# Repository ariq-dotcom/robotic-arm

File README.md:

Repository ini berisi file-file pengembangan robot arm 5 DOF berbasis Arduino Mega, meliputi desain elektrikal (PCB), program kendali

Pada folder ARM KENDALI, setiap angka pada nama file .ino menunjukkan urutan perkembangan dan pembaruan program sejak tahap awal pengembangan ketika isi program masih berupa struktur dasar dan belum sepenuhnya siap digunakan. File dengan angka terbesar merupakan program versi terbaru.

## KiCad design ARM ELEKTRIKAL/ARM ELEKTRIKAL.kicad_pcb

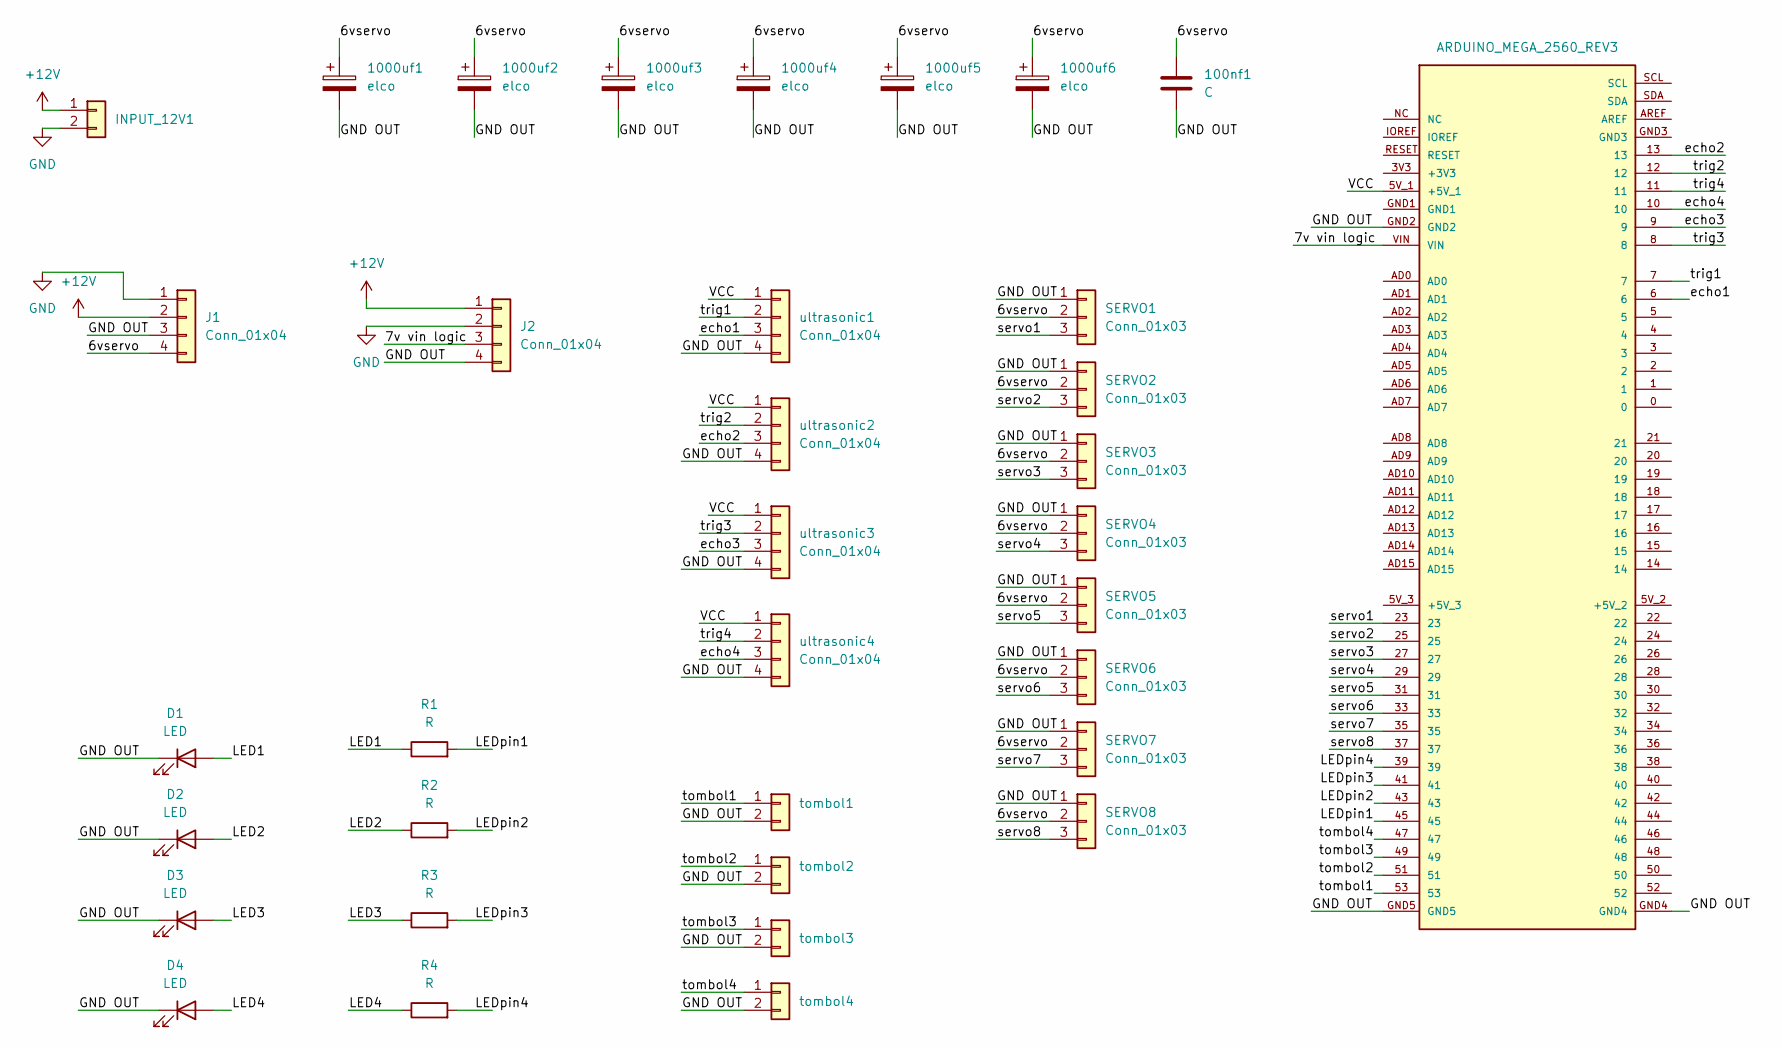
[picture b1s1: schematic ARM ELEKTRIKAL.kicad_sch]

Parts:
100nf1: C; C_Rect_L9.0mm_W2.7mm_P7.50mm_MKT
1000uf1, 1000uf2, 1000uf3, 1000uf4, 1000uf5, 1000uf6: elco; CP_Radial_D10.0mm_P5.00mm
A1: ARDUINO_MEGA_2560_REV3; ARDUINO_ARDUINO_MEGA_2560_REV3; PARTREV 3
D1, D2, D3, D4: LED; PinHeader_1x02_P2.54mm_Vertical
INPUT_12V1: Conn_01x02; TerminalBlock_MetzConnect_Type171_RT13702HBWC_1x02_P7.50mm_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
J1, J2: Conn_01x04; TerminalBlock_MetzConnect_Type171_RT13704HBWC_1x04_P7.50mm_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
R1, R2, R3, R4: R; R_Axial_DIN0204_L3.6mm_D1.6mm_P7.62mm_Horizontal
SERVO1, SERVO2, SERVO3, SERVO4, SERVO5, SERVO6, SERVO7, SERVO8: Conn_01x03; PinHeader_1x03_P2.54mm_Vertical
tombol1, tombol2, tombol3, tombol4: Conn_01x02; PinHeader_1x02_P2.54mm_Vertical
ultrasonic1, ultrasonic2, ultrasonic3, ultrasonic4: Conn_01x04; PinHeader_1x04_P2.54mm_Vertical

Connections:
+12V: INPUT_12V1.1, J1.2, J2.1
/6vservo: 100nf1.1, 1000uf1.1, 1000uf2.1, 1000uf3.1, 1000uf4.1, 1000uf5.1, 1000uf6.1, J1.4, SERVO1.2, SERVO2.2, SERVO3.2, SERVO4.2, SERVO5.2, SERVO6.2, SERVO7.2, SERVO8.2
/7v vin logic: A1.VIN, J2.3
/GND OUT: 100nf1.2, 1000uf1.2, 1000uf2.2, 1000uf3.2, 1000uf4.2, 1000uf5.2, 1000uf6.2, A1.GND2, A1.GND4, A1.GND5, D1.1 (K), D2.1 (K), D3.1 (K), D4.1 (K), J1.3, J2.4, SERVO1.1, SERVO2.1, SERVO3.1, SERVO4.1, SERVO5.1, SERVO6.1, SERVO7.1, SERVO8.1, tombol1.2, tombol2.2, tombol3.2, tombol4.2, ultrasonic1.4, ultrasonic2.4, ultrasonic3.4, ultrasonic4.4
/LED1: D1.2 (A), R1.1
/LED2: D2.2 (A), R2.1
/LED3: D3.2 (A), R3.1
/LED4: D4.2 (A), R4.1
/LEDpin1: A1.45, R1.2
/LEDpin2: A1.43, R2.2
/LEDpin3: A1.41, R3.2
/LEDpin4: A1.39, R4.2
/VCC: A1.5V_1 (+5V_1), ultrasonic1.1, ultrasonic2.1, ultrasonic3.1, ultrasonic4.1
/echo1: A1.6, ultrasonic1.3
/echo2: A1.13, ultrasonic2.3
/echo3: A1.9, ultrasonic3.3
/echo4: A1.10, ultrasonic4.3
/servo1: A1.23, SERVO1.3
/servo2: A1.25, SERVO2.3
/servo3: A1.27, SERVO3.3
/servo4: A1.29, SERVO4.3
/servo5: A1.31, SERVO5.3
/servo6: A1.33, SERVO6.3
/servo7: A1.35, SERVO7.3
/servo8: A1.37, SERVO8.3
/tombol1: A1.53, tombol1.1
/tombol2: A1.51, tombol2.1
/tombol3: A1.49, tombol3.1
/tombol4: A1.47, tombol4.1
/trig1: A1.7, ultrasonic1.2
/trig2: A1.12, ultrasonic2.2
/trig3: A1.8, ultrasonic3.2
/trig4: A1.11, ultrasonic4.2
GND: INPUT_12V1.2, J1.1, J2.2

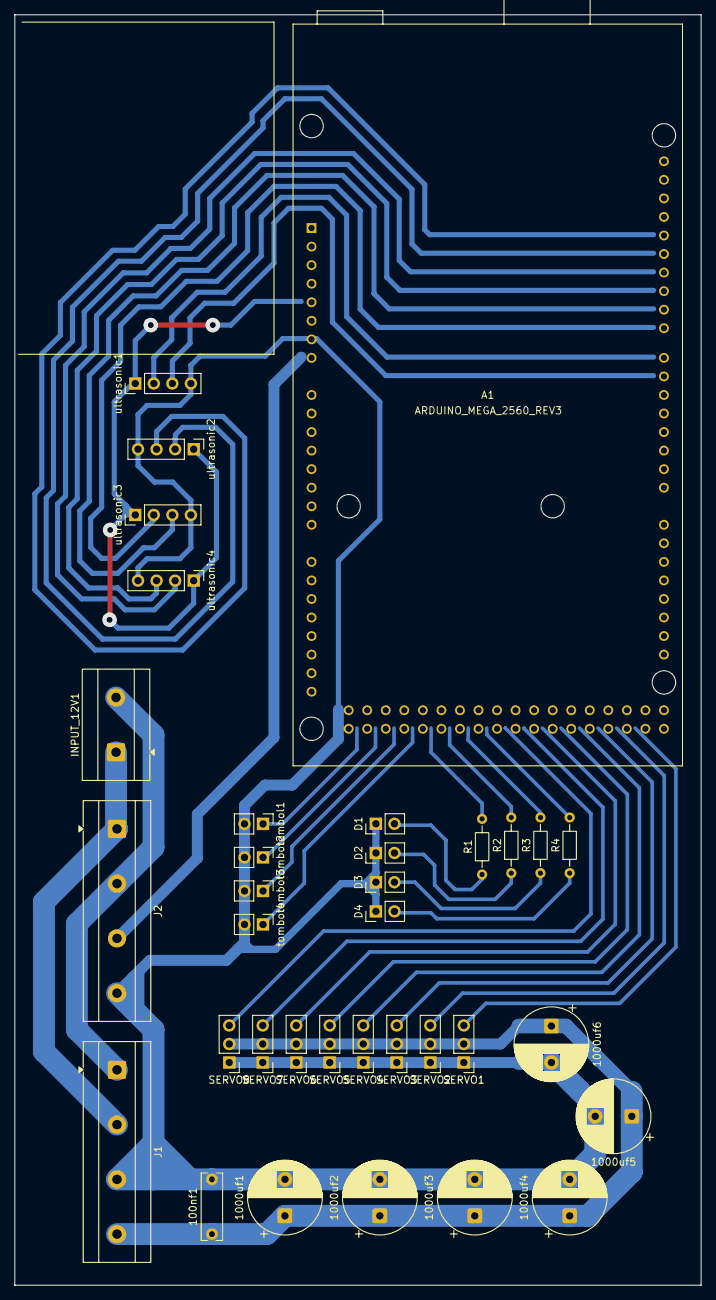
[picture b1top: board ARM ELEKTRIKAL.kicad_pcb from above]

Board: 2 copper layers, 94.0 x 174.0 mm, 35 parts (0 on the bottom side), 34 nets.
